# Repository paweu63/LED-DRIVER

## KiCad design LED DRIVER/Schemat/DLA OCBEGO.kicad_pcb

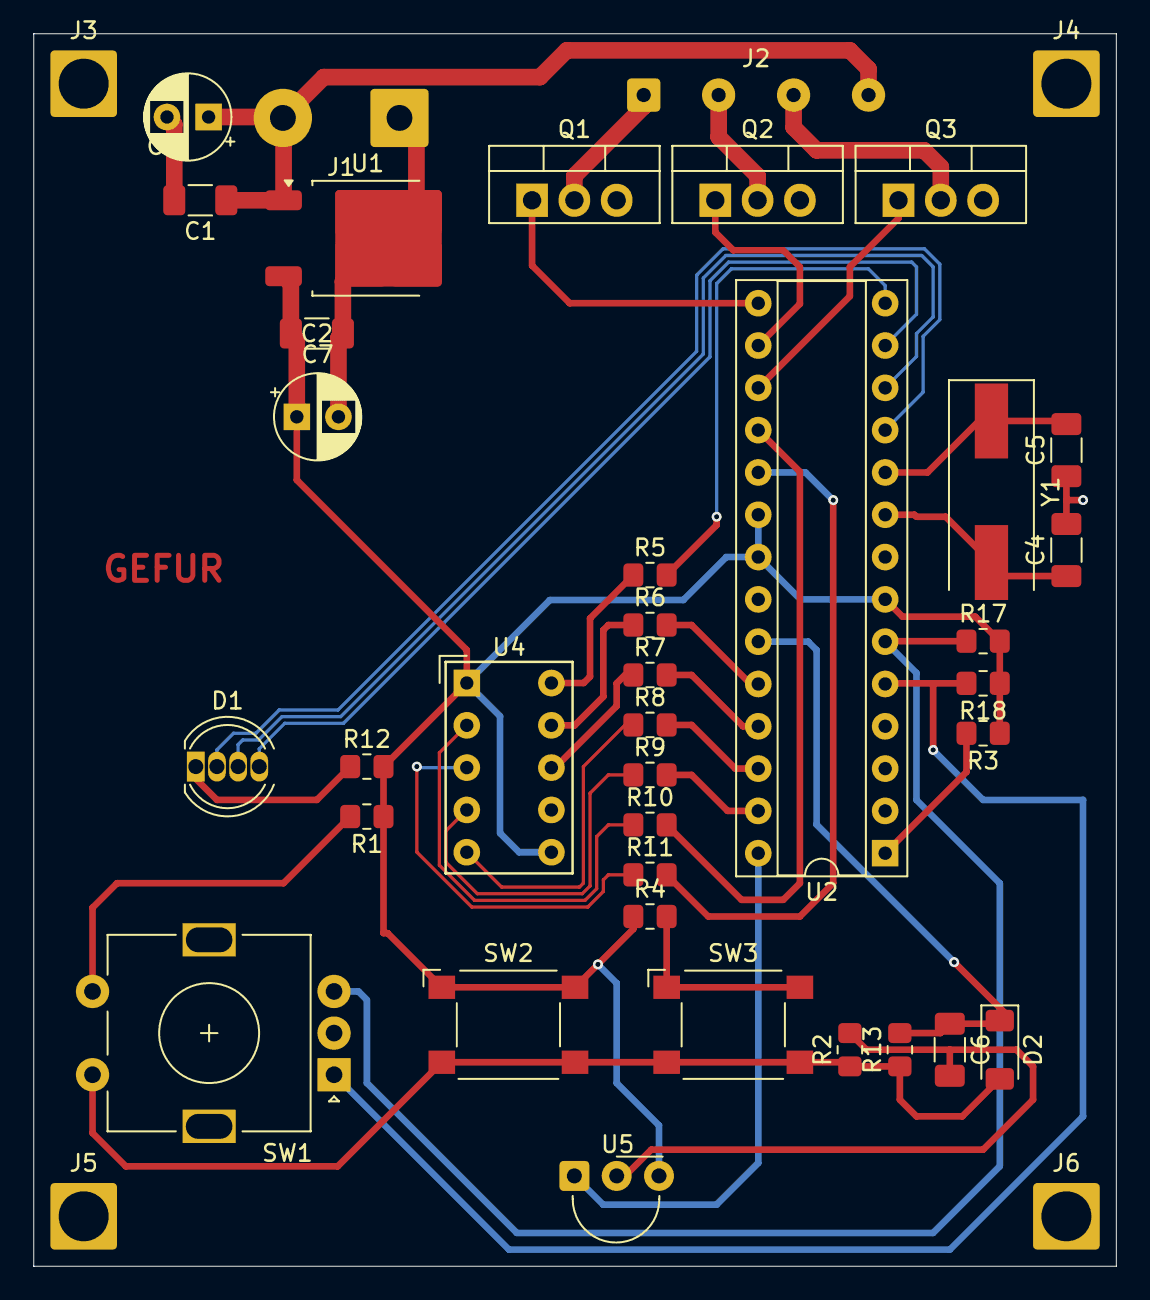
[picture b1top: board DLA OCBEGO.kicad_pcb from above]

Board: 2 copper layers, 65.0 x 74.0 mm, 41 parts (0 on the bottom side), 37 nets.

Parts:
C1: 0.33uF; C_1206_3216Metric_Pad1.33x1.80mm_HandSolder
C2: 0.1uF; C_1206_3216Metric_Pad1.33x1.80mm_HandSolder
C3: 100uF 25V; CP_Radial_D5.0mm_P2.50mm
C4, C5: 22pF; C_1206_3216Metric_Pad1.33x1.80mm_HandSolder
C6: 1uF; C_1206_3216Metric_Pad1.33x1.80mm_HandSolder
C7: 10uF 25V; CP_Radial_D5.0mm_P2.50mm
D1: LED_ARGB; LED_D5.0mm-4_RGB
D2: D; D_MiniMELF
J1: Conn_01x02; SolderWire-0.75sqmm_1x02_P7mm_D1.25mm_OD3.5mm
J2: Conn_01x04_Socket; SolderWire-0.25sqmm_1x04_P4.5mm_D0.65mm_OD2mm
J3, J4, J5, J6: Conn_01x01_Pin; SolderWire-2.5sqmm_1x01_D2.4mm_OD3.6mm
Q1, Q2, Q3: IRF740; TO-220-3_Vertical
R1: 15k; R_0805_2012Metric_Pad1.20x1.40mm_HandSolder
R2, R3, R17, R18: 10k; R_0805_2012Metric_Pad1.20x1.40mm_HandSolder
R4: 4,7k; R_0805_2012Metric_Pad1.20x1.40mm_HandSolder
R5, R6, R7, R8, R9, R10, R11, R12: 220; R_0805_2012Metric_Pad1.20x1.40mm_HandSolder
R13: 470; R_0805_2012Metric_Pad1.20x1.40mm_HandSolder
SW1: RotaryEncoder_Switch_MP; RotaryEncoder_Alps_EC11E-Switch_Vertical_H20mm
SW2, SW3: SW_Omron_B3FS; SW_SPST_Omron_B3FS-100xP
U1: LM78M05_TO252; TO-252-2
U2: ATmega328-P; DIP-28_W7.62mm_Socket
U4: HDSP-7501; HDSP-A151
U5: TSOP531xx; Vishay_MINIMOLD-3Pin
Y1: 16MHz; Crystal_SMD_HC49-SD

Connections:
+5V: C2.1, C7.1, R1.1, R3.1, R4.1, R12.2, R17.2, R18.1, SW2.1, U1.3 (VO), U2.7 (VCC), U2.20 (AVCC), U2.21 (AREF), U4.1 (CA), U4.6 (CA), U5.3 (Vs)
+12V: C1.1, C3.1, J1.2, J2.4, U1.1 (VI)
GND: C1.2, C2.2, C3.2, C4.2, C5.1, C6.2, C7.2, J1.1, J3.1, J4.1, J5.1, J6.1, Q1.3 (S), Q2.3 (S), Q3.3 (S), R2.2, SW1.C, SW1.MP, U1.2 (GND), U2.8 (GND), U2.22 (GND), U4.7 (DP), U5.2 (GND)
unnamed: D1.1 (A), R12.1
unnamed: D1.4 (BK), U2.13 (PD7)
unnamed: D1.3 (GK), U2.12 (PD6)
unnamed: D1.2 (RK), U2.11 (PD5)
unnamed: D2.2 (A), R2.1, R13.1, SW1.S2, SW2.2, SW3.2
unnamed: C6.1, D2.1 (K), R13.2, U2.23 (PC0)
unnamed: J2.1, Q1.2 (D)
unnamed: J2.2, Q2.2 (D)
unnamed: J2.3, Q3.2 (D)
unnamed: Q1.1 (G), U2.15 (PB1)
unnamed: Q2.1 (G), U2.16 (PB2)
unnamed: Q3.1 (G), U2.17 (PB3)
unnamed: R1.2, SW1.S1
unnamed: R4.2, SW3.1
unnamed: R5.2, U2.14 (PB0)
unnamed: R10.2, U2.18 (PB4)
unnamed: R11.2, U2.19 (PB5)
unnamed: R6.2, U2.24 (PC1)
unnamed: R7.2, U2.25 (PC2)
unnamed: R8.2, U2.26 (PC3)
unnamed: R9.2, U2.27 (PC4)
unnamed: U2.28 (PC5), U5.1 (OUT)
unnamed: R18.2, SW1.A, U2.5 (PD3)
unnamed: R17.1, SW1.B, U2.6 (PD4)
unnamed: C4.1, U2.9 (XTAL1/PB6), Y1.2
unnamed: C5.2, U2.10 (XTAL2/PB7), Y1.1
unnamed: R3.2, U2.1 (~RESET/PC6)
unnamed: R5.1, U4.10 (A)
unnamed: R6.1, U4.9 (B)
unnamed: R7.1, U4.8 (C)
unnamed: R8.1, U4.5 (D)
unnamed: R9.1, U4.4 (E)
unnamed: R10.1, U4.2 (F)
unnamed: R11.1, U4.3 (G)

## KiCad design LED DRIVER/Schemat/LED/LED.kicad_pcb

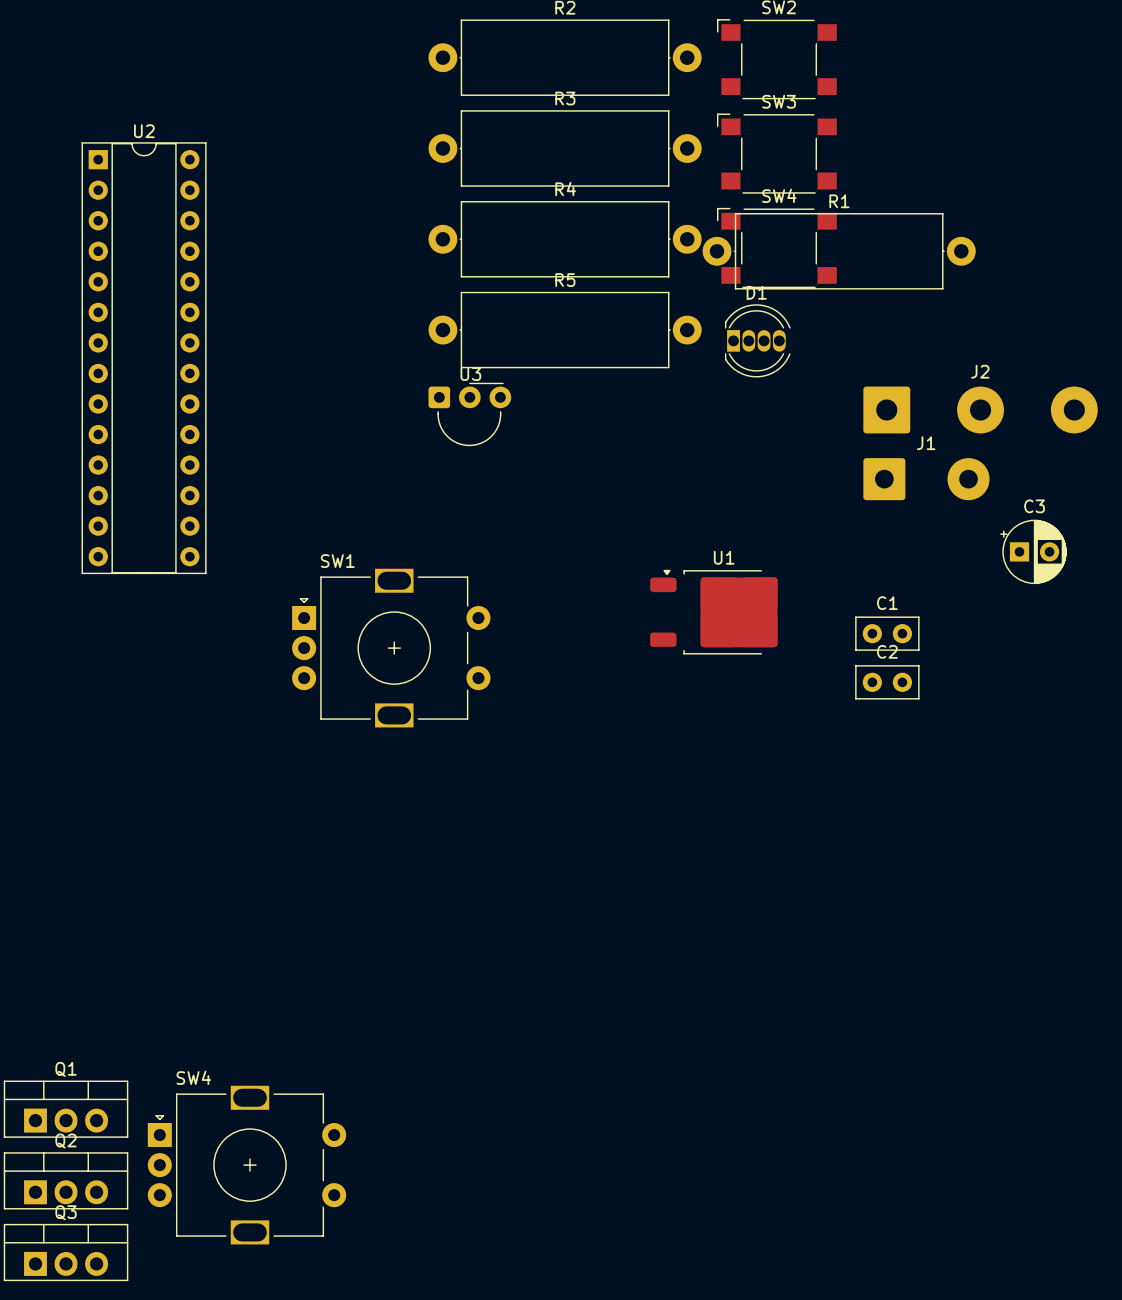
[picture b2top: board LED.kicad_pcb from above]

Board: 2 copper layers, 22 parts (0 on the bottom side), 12 nets, no tracks yet.

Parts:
C1: 0.33uF; C_Disc_D5.0mm_W2.5mm_P2.50mm
C2: 0.1uF; C_Disc_D5.0mm_W2.5mm_P2.50mm
C3: C_Polarized; CP_Radial_D5.0mm_P2.50mm
D1: LED_ARGB; LED_D5.0mm-4_RGB
J1: Conn_01x02; SolderWire-0.75sqmm_1x02_P7mm_D1.25mm_OD3.5mm
J2: Conn_01x03_Pin; SolderWire-1sqmm_1x03_P7.8mm_D1.4mm_OD3.9mm
Q1, Q2, Q3: IRF740; TO-220-3_Vertical
R1, R2, R3: 10k; R_Axial_DIN0617_L17.0mm_D6.0mm_P20.32mm_Horizontal
R4: 6,8k; R_Axial_DIN0617_L17.0mm_D6.0mm_P20.32mm_Horizontal
R5: 39k; R_Axial_DIN0617_L17.0mm_D6.0mm_P20.32mm_Horizontal
SW1, SW4#2: RotaryEncoder_Switch_MP; RotaryEncoder_Alps_EC11E-Switch_Vertical_H20mm
SW2, SW3, SW4: SW_Omron_B3FS; SW_SPST_Omron_B3FS-100xP
U1: LM78M05_TO252; TO-252-2
U2: ATmega328-P; DIP-28_W7.62mm_Socket
U3: TSOP21xx; Vishay_MINIMOLD-3Pin

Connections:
+5V: C2.1, R1.1, R2.1, R4.1, R5.1, SW2.1, SW3.1, SW4.1, U1.3 (VO), U2.7 (VCC), U2.20 (AVCC)
+12V: C1.1, C3.1, J1.2, U1.1 (VI)
GND: C1.2, C2.2, C3.2, J1.1, Q1.3 (S), Q2.3 (S), Q3.3 (S), R3.2, U1.2 (GND), U2.8 (GND), U2.22 (GND)
unnamed: J2.1, Q3.2 (D)
unnamed: J2.2, Q2.2 (D)
unnamed: J2.3, Q1.2 (D)
unnamed: Q1.1 (G), U2.15 (PB1)
unnamed: Q2.1 (G), U2.16 (PB2)
unnamed: Q3.1 (G), U2.17 (PB3)
unnamed: R5.2, SW4.2
unnamed: R3.1, R4.2, SW2.2, SW3.2, U2.23 (PC0)
unnamed: R1.2, U2.1 (~RESET/PC6)

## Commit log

2025-04-25 Schemat
2025-04-25 Zdjecia projektu
2025-04-25 Reszta
2025-08-27 Totaly new code
2025-10-30 Basic code finished
2025-10-30 mlocek update
2025-10-30 mlocek delete
2025-11-01 dodanie zmiany jasności i poprwa kodów pilota
2025-11-01 increment/decrement enkoder+IR
2025-11-23 Add rainbow function to KOD_V2.1.ino
